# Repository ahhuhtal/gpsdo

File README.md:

# GPS discliplined oscillator

Contained in this repository are the source code and PCB design files for my GPS disciplined oscillator project.

The GPSDO uses the one pulse per second (PPS) output of a GPS receiver to continuously adjust an OSC5A2B02 oven-controller crystal oscillator to keep it phase-locked with GPS time.

This gives a stable (both short term and long) 10 MHz time base for measurement instruments.

An important design goal has been to keep the cost very low.

Some more information is available at https://kiedontaa.blogspot.com/2025/02/gps-disciplined-oscillator-part-2.html

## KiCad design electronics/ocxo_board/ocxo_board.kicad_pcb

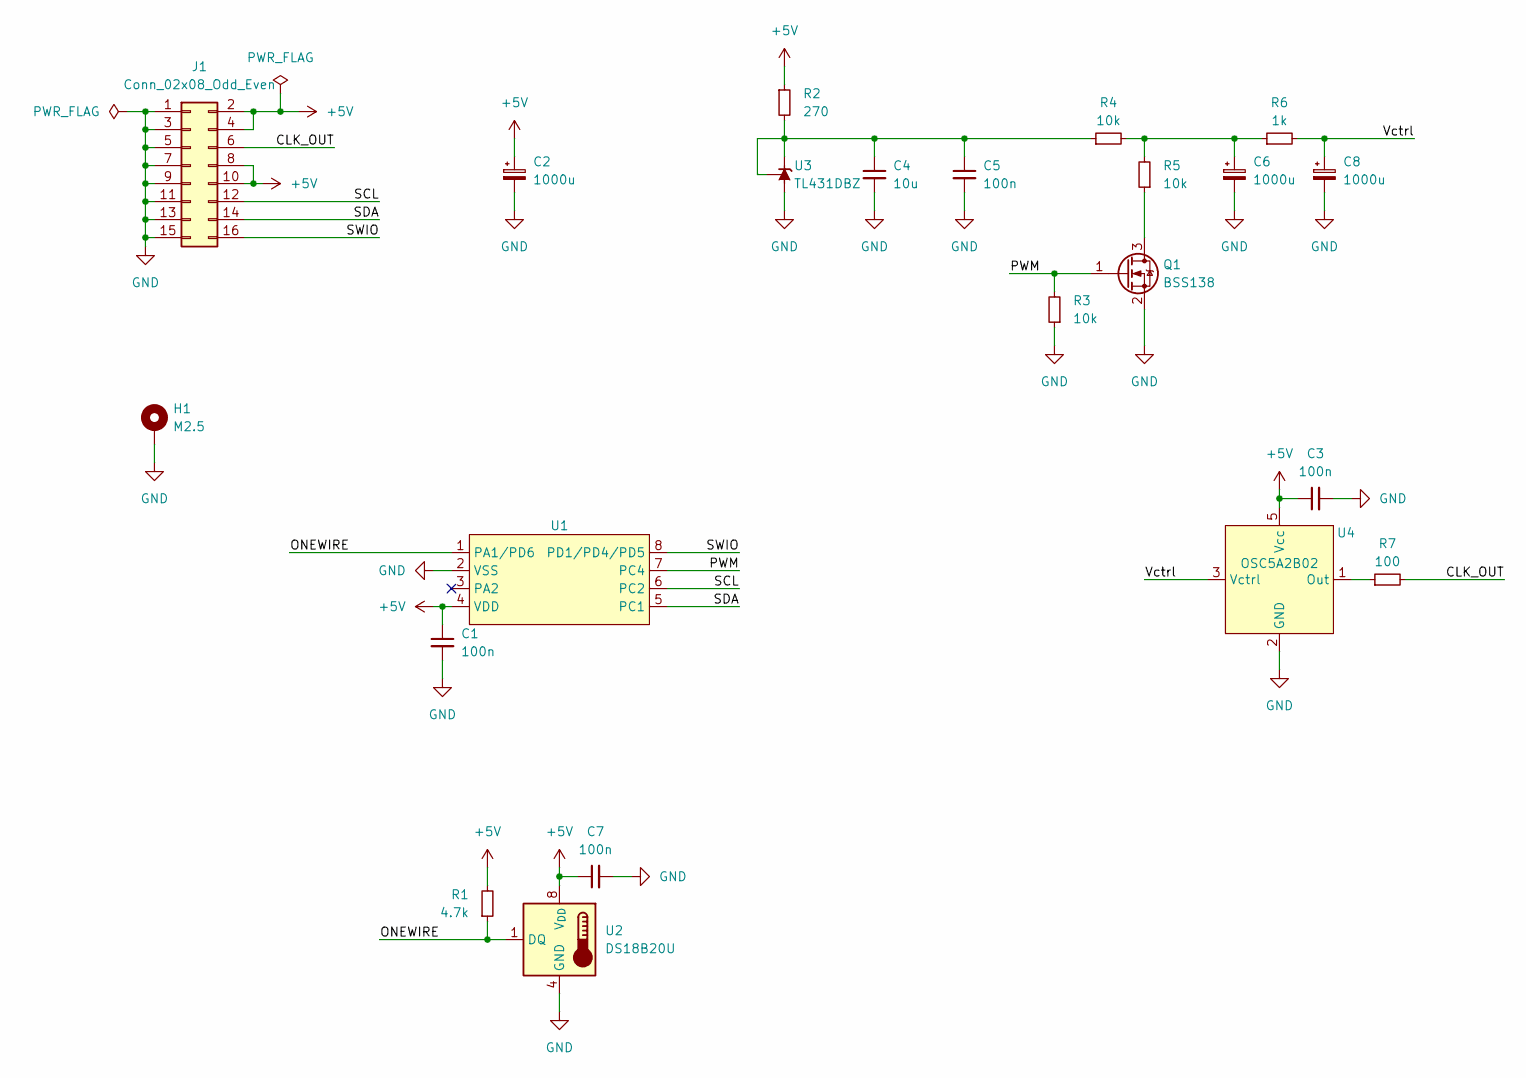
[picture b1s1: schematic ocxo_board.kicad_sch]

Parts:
C1, C3, C5, C7: 100n; C_0805_2012Metric_Pad1.18x1.45mm_HandSolder
C2, C6, C8: 1000u; CP_Radial_D8.0mm_P3.50mm
C4: 10u; C_0805_2012Metric_Pad1.18x1.45mm_HandSolder
H1: M2.5; MountingHole_2.7mm_M2.5_DIN965_Pad
J1: Conn_02x08_Odd_Even; IDC-Header_2x08_P2.54mm_Vertical
Q1: BSS138; SOT-23
R1: 4.7k; R_0805_2012Metric_Pad1.20x1.40mm_HandSolder
R2: 270; R_0805_2012Metric_Pad1.20x1.40mm_HandSolder
R3, R4, R5: 10k; R_0805_2012Metric_Pad1.20x1.40mm_HandSolder
R6: 1k; R_0805_2012Metric_Pad1.20x1.40mm_HandSolder
R7: 100; R_0805_2012Metric_Pad1.20x1.40mm_HandSolder
U1: SOP-8_3.9x4.9mm_P1.27mm
U2: DS18B20U; MSOP-8_3x3mm_P0.65mm
U3: TL431DBZ; SOT-23
U4: OSC5A2B02

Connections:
+5V: C1.1, C2.1, C3.1, C7.1, J1.2, J1.4, J1.8, J1.10, R1.2, R2.1, U1.4 (VDD), U2.8 (V_{DD}), U4.5 (Vcc)
/CLK_OUT: J1.6, R7.2
/ONEWIRE: R1.1, U1.1 (PA1/PD6), U2.1 (DQ)
/PWM: Q1.1 (G), R3.2, U1.7 (PC4)
/SCL: J1.12, U1.6 (PC2)
/SDA: J1.14, U1.5 (PC1)
/SWIO: J1.16, U1.8 (PD1/PD4/PD5)
/Vctrl: C8.1, R6.2, U4.3 (Vctrl)
GND: C1.2, C2.2, C3.2, C4.2, C5.2, C6.2, C7.2, C8.2, H1.1, J1.1, J1.3, J1.5, J1.7, J1.9, J1.11, J1.13, J1.15, Q1.2 (S), R3.1, U1.2 (VSS), U2.4 (GND), U3.3 (A), U4.2 (GND)
unnamed: C6.1, R4.2, R5.2, R6.1
unnamed: Q1.3 (D), R5.1
unnamed: C4.1, C5.1, R2.2, R4.1, U3.1 (K), U3.2 (REF)
unnamed: R7.1, U4.1 (Out)

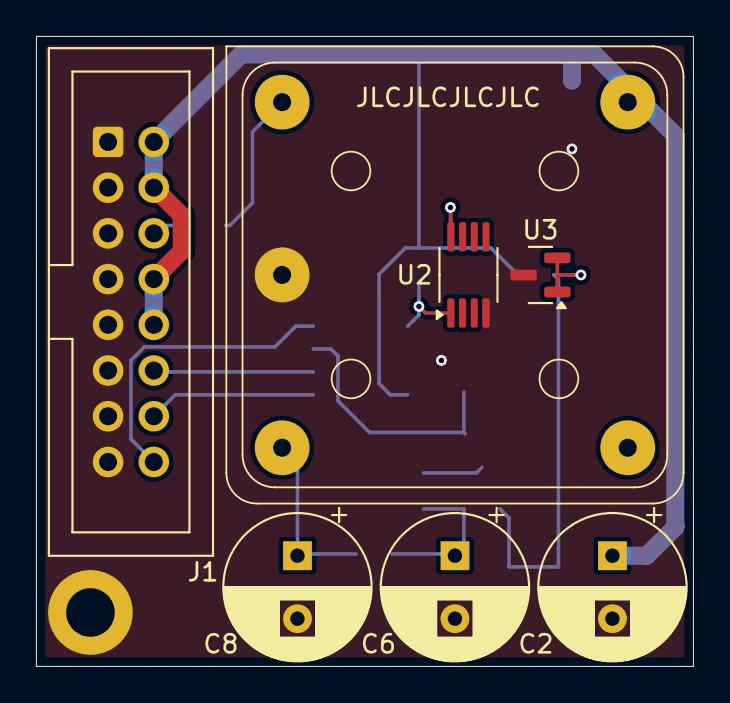
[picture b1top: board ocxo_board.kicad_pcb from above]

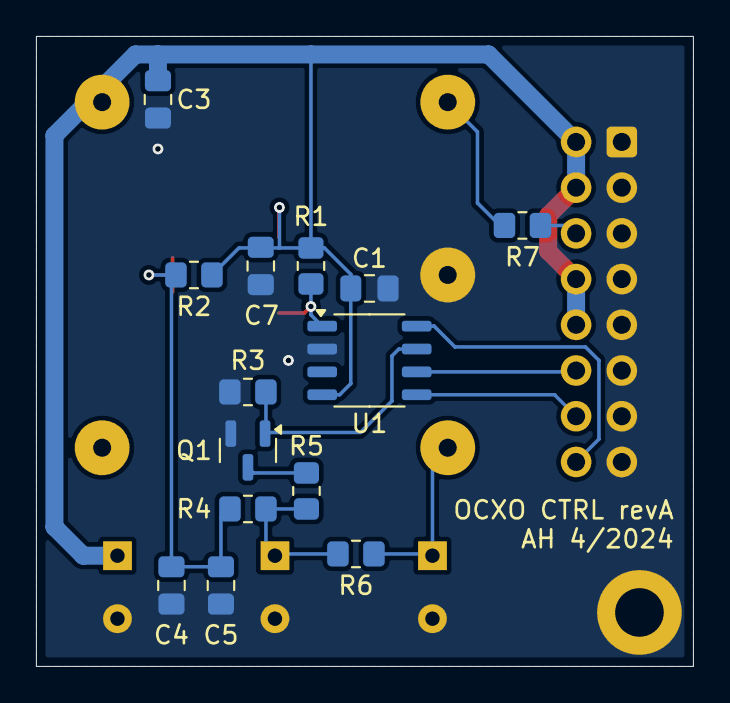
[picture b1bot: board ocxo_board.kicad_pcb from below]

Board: 2 copper layers, 36.5 x 35.0 mm, 22 parts (14 on the bottom side), 13 nets.

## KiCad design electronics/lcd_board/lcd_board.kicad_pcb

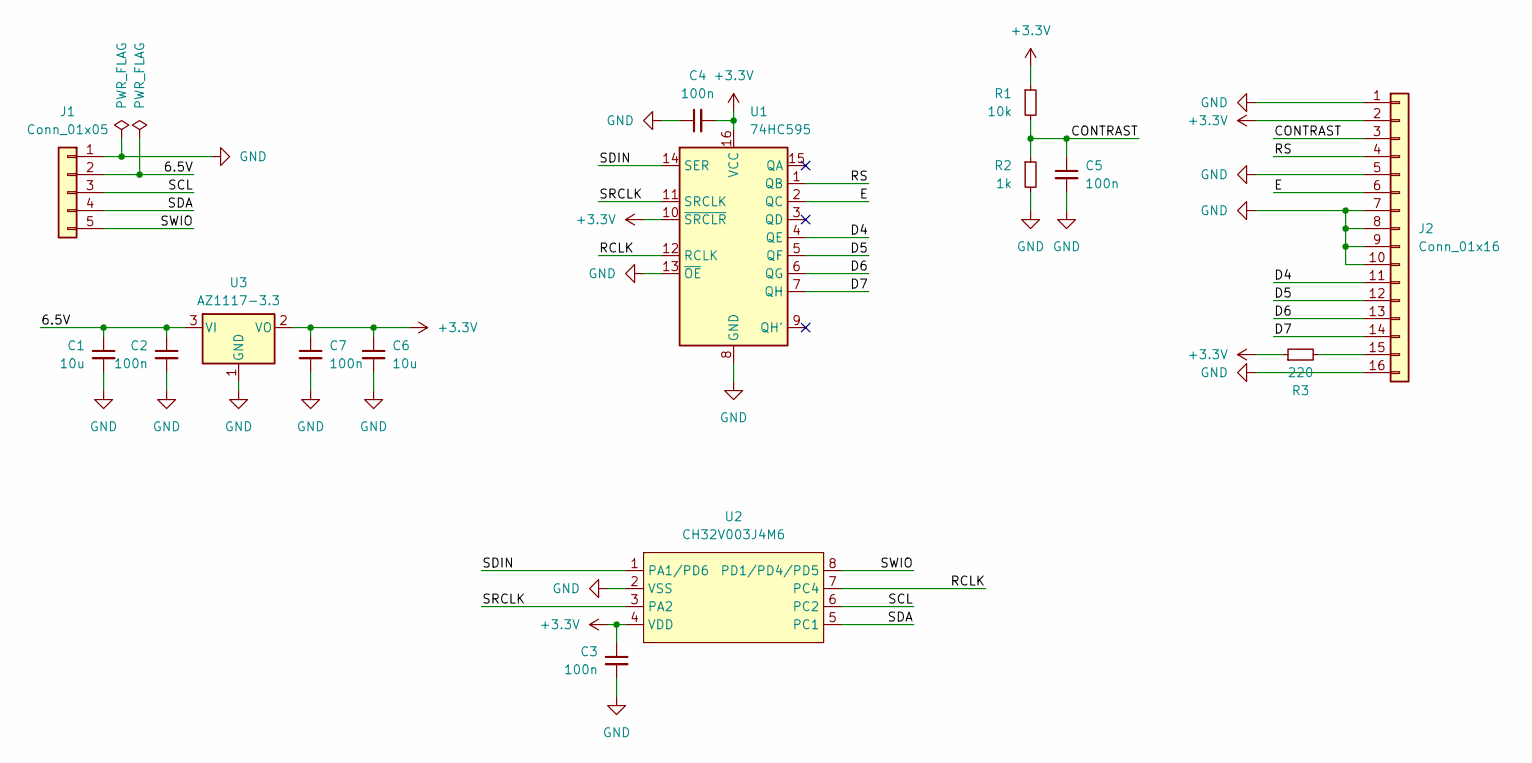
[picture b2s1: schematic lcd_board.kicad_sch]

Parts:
C1, C6: 10u; C_0805_2012Metric_Pad1.18x1.45mm_HandSolder
C2, C3, C4, C5, C7: 100n; C_0805_2012Metric_Pad1.18x1.45mm_HandSolder
J1: Conn_01x05; JST_PH_B5B-PH-K_1x05_P2.00mm_Vertical
J2: Conn_01x16; PinHeader_1x16_P2.54mm_Vertical
R1: 10k; R_0805_2012Metric_Pad1.20x1.40mm_HandSolder
R2: 1k; R_0805_2012Metric_Pad1.20x1.40mm_HandSolder
R3: 220; R_0805_2012Metric_Pad1.20x1.40mm_HandSolder
U1: 74HC595; SOIC-16_3.9x9.9mm_P1.27mm
U2: CH32V003J4M6; SOP-8_3.9x4.9mm_P1.27mm
U3: AZ1117-3.3; SOT-223-3_TabPin2

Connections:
+3.3V: C3.1, C4.2, C6.1, C7.1, J2.2, R1.1, R3.1, U1.10 (~SRCLR), U1.16 (VCC), U2.4 (VDD), U3.2 (VO)
/6.5V: C1.1, C2.1, J1.2, U3.3 (VI)
/CONTRAST: C5.1, J2.3, R1.2, R2.1
/D4: J2.11, U1.4 (QE)
/D5: J2.12, U1.5 (QF)
/D6: J2.13, U1.6 (QG)
/D7: J2.14, U1.7 (QH)
/E: J2.6, U1.2 (QC)
/RCLK: U1.12 (RCLK), U2.7 (PC4)
/RS: J2.4, U1.1 (QB)
/SCL: J1.3, U2.6 (PC2)
/SDA: J1.4, U2.5 (PC1)
/SDIN: U1.14 (SER), U2.1 (PA1/PD6)
/SRCLK: U1.11 (SRCLK), U2.3 (PA2)
/SWIO: J1.5, U2.8 (PD1/PD4/PD5)
GND: C1.2, C2.2, C3.2, C4.1, C5.2, C6.2, C7.2, J1.1, J2.1, J2.5, J2.7, J2.8, J2.9, J2.10, J2.16, R2.2, U1.8 (GND), U1.13 (~OE), U2.2 (VSS), U3.1 (GND)
unnamed: J2.15, R3.2

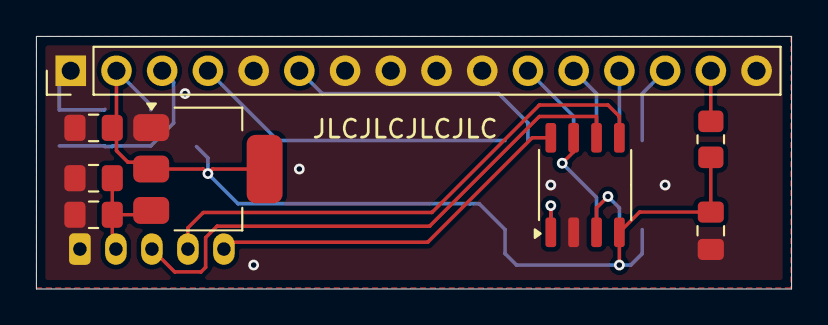
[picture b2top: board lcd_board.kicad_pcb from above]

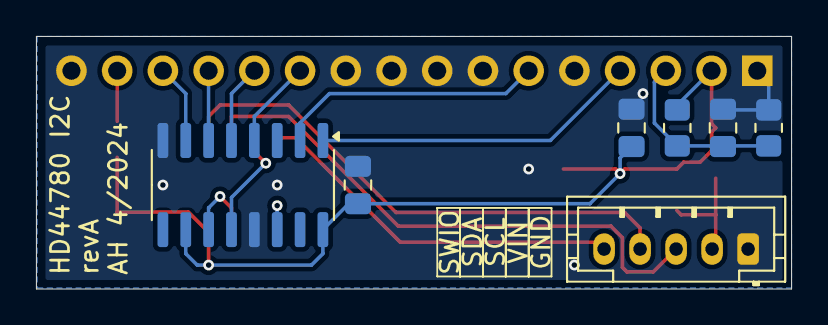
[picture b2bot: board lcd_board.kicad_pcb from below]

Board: 2 copper layers, 41.9 x 14.0 mm, 15 parts (7 on the bottom side), 17 nets.

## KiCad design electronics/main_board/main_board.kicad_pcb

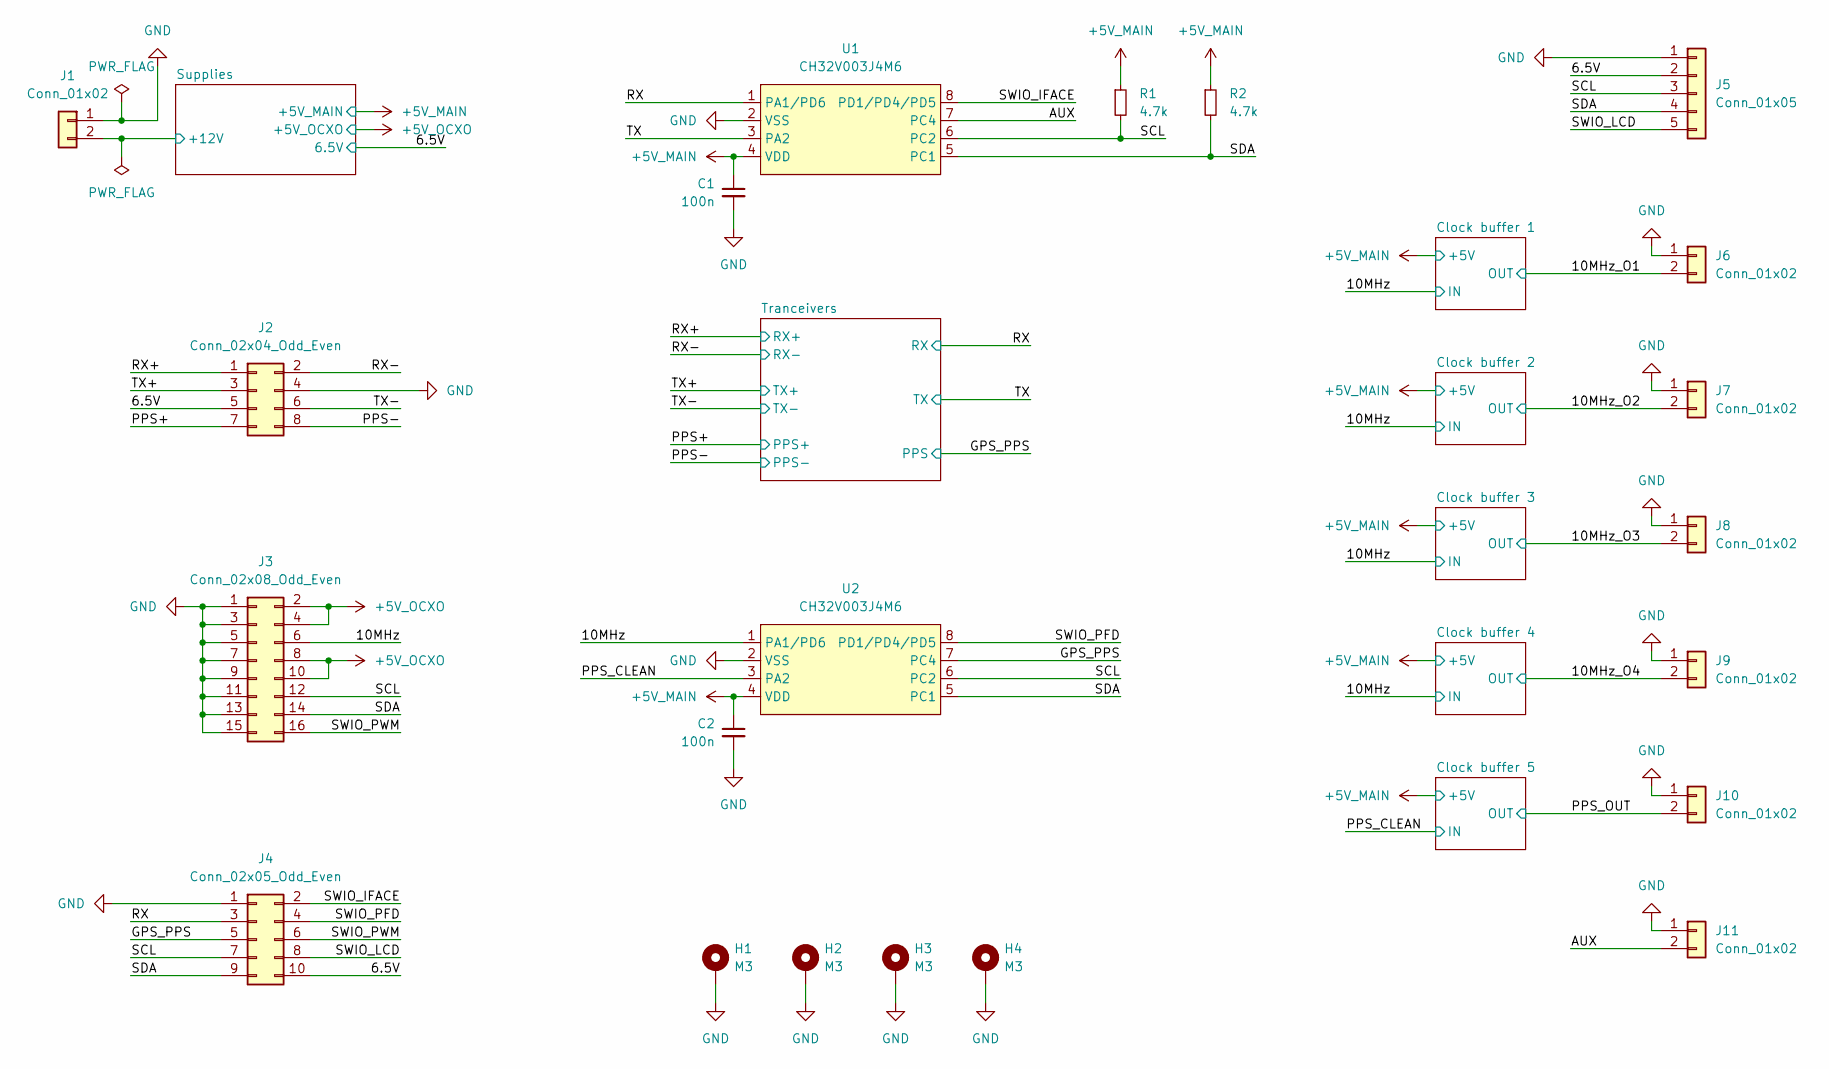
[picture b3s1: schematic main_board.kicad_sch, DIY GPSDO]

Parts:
C1, C2: 100n; C_0805_2012Metric_Pad1.18x1.45mm_HandSolder
H1, H2, H3, H4: M3; MountingHole_3.2mm_M3_DIN965_Pad
J1, J6, J7, J8, J9, J10, J11: Conn_01x02; JST_PH_B2B-PH-K_1x02_P2.00mm_Vertical
J2: Conn_02x04_Odd_Even; IDC-Header_2x04_P2.54mm_Vertical
J3: Conn_02x08_Odd_Even; IDC-Header_2x08_P2.54mm_Vertical
J4: Conn_02x05_Odd_Even; IDC-Header_2x05_P2.54mm_Vertical
J5: Conn_01x05; JST_PH_B5B-PH-K_1x05_P2.00mm_Vertical
R1, R2: 4.7k; R_0805_2012Metric_Pad1.20x1.40mm_HandSolder
U1, U2: CH32V003J4M6; SOP-8_3.9x4.9mm_P1.27mm

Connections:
+5V_MAIN: C1.1, C2.1, R1.1, R2.1, U1.4 (VDD), U2.4 (VDD); also elsewhere on the board
+5V_OCXO: J3.2, J3.4, J3.8, J3.10; also elsewhere on the board
/6.5V: J2.5, J4.10, J5.2; also elsewhere on the board
/10MHz: J3.6, U2.1 (PA1/PD6); also elsewhere on the board
/10MHz_O1: J6.2; also elsewhere on the board
/10MHz_O2: J7.2; also elsewhere on the board
/10MHz_O3: J8.2; also elsewhere on the board
/10MHz_O4: J9.2; also elsewhere on the board
/AUX: J11.2, U1.7 (PC4)
/GPS_PPS: J4.5, U2.7 (PC4); also elsewhere on the board
/PPS+: J2.7; also elsewhere on the board
/PPS-: J2.8; also elsewhere on the board
/PPS_CLEAN: U2.3 (PA2); also elsewhere on the board
/PPS_OUT: J10.2; also elsewhere on the board
/RX: J4.3, U1.1 (PA1/PD6); also elsewhere on the board
/RX+: J2.1; also elsewhere on the board
/RX-: J2.2; also elsewhere on the board
/SCL: J3.12, J4.7, J5.3, R1.2, U1.6 (PC2), U2.6 (PC2)
/SDA: J3.14, J4.9, J5.4, R2.2, U1.5 (PC1), U2.5 (PC1)
/SWIO_IFACE: J4.2, U1.8 (PD1/PD4/PD5)
/SWIO_LCD: J4.8, J5.5
/SWIO_PFD: J4.4, U2.8 (PD1/PD4/PD5)
/SWIO_PWM: J3.16, J4.6
/Supplies/+12V: J1.2; also elsewhere on the board
/TX: U1.3 (PA2); also elsewhere on the board
/TX+: J2.3; also elsewhere on the board
/TX-: J2.6; also elsewhere on the board
GND: C1.2, C2.2, H1.1, H2.1, H3.1, H4.1, J1.1, J2.4, J3.1, J3.3, J3.5, J3.7, J3.9, J3.11, J3.13, J3.15, J4.1, J5.1, J6.1, J7.1, J8.1, J9.1, J10.1, J11.1, U1.2 (VSS), U2.2 (VSS); also elsewhere on the board

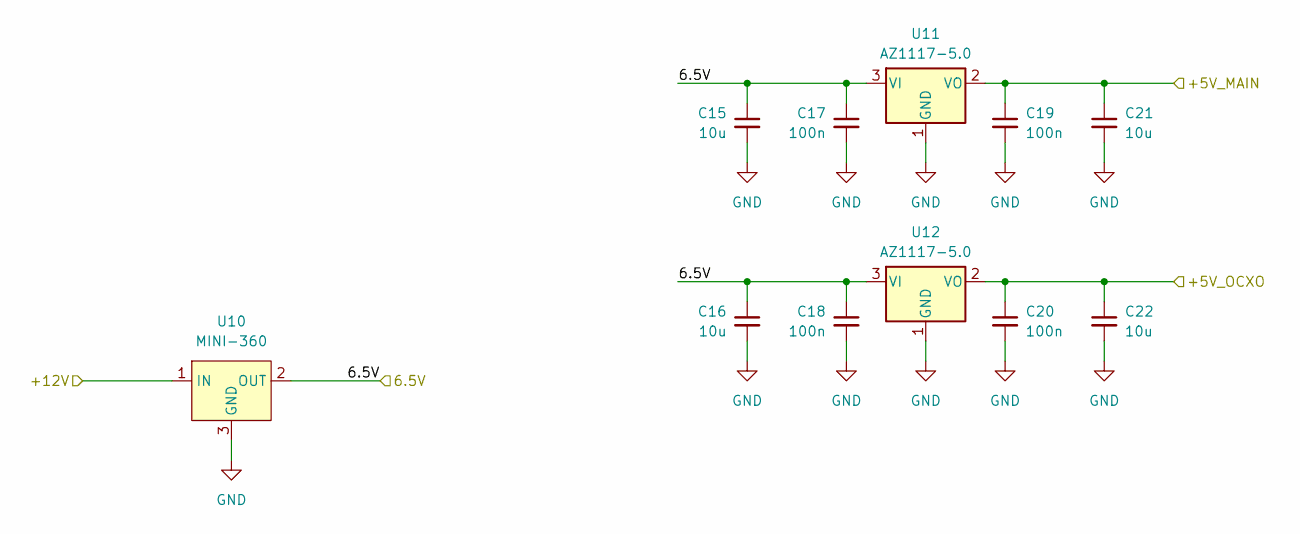
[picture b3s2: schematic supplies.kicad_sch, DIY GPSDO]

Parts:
C15, C16, C21, C22: 10u; C_0805_2012Metric_Pad1.18x1.45mm_HandSolder
C17, C18, C19, C20: 100n; C_0805_2012Metric_Pad1.18x1.45mm_HandSolder
U10: MINI-360
U11, U12: AZ1117-5.0; TO-252-2

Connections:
+5V_MAIN: C19.1, C21.1, U11.2 (VO); also elsewhere on the board
+5V_OCXO: C20.1, C22.1, U12.2 (VO); also elsewhere on the board
/6.5V: C15.1, C16.1, C17.1, C18.1, U10.2 (OUT), U11.3 (VI), U12.3 (VI); also elsewhere on the board
/Supplies/+12V: U10.1 (IN); also elsewhere on the board
GND: C15.2, C16.2, C17.2, C18.2, C19.2, C20.2, C21.2, C22.2, U10.3 (GND), U11.1 (GND), U12.1 (GND); also elsewhere on the board

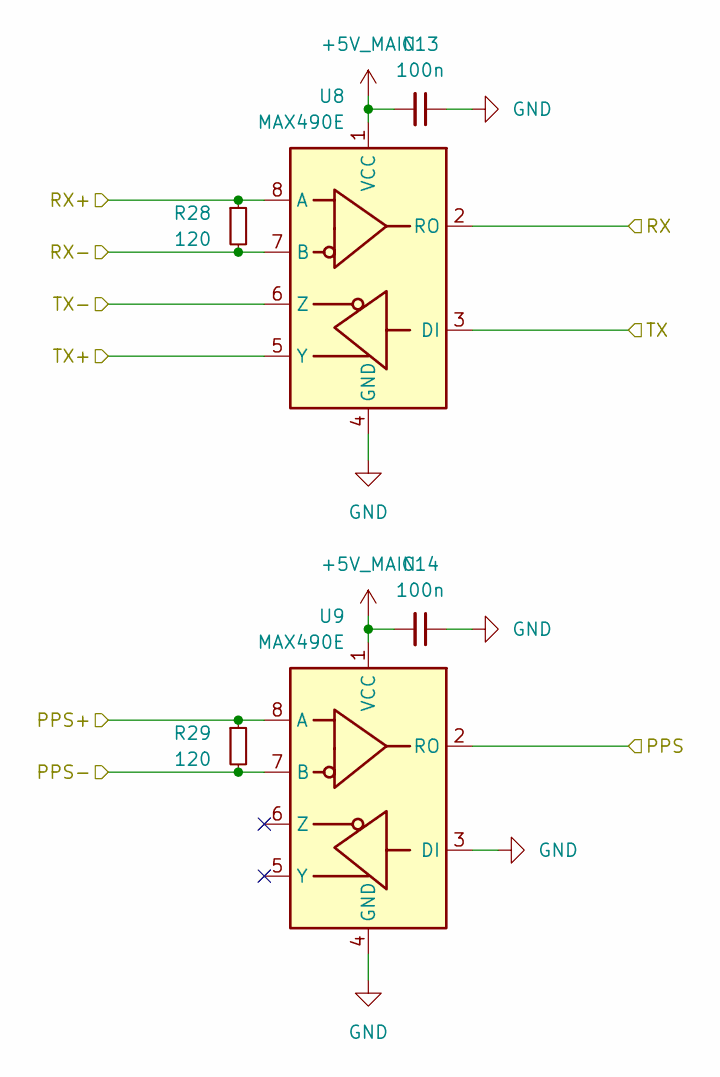
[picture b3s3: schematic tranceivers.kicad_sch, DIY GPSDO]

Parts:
C13, C14: 100n; C_0805_2012Metric_Pad1.18x1.45mm_HandSolder
R28, R29: 120; R_0805_2012Metric_Pad1.20x1.40mm_HandSolder
U8, U9: MAX490E; SOIC-8_3.9x4.9mm_P1.27mm

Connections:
+5V_MAIN: C13.2, C14.2, U8.1 (VCC), U9.1 (VCC); also elsewhere on the board
/GPS_PPS: U9.2 (RO); also elsewhere on the board
/PPS+: R29.1, U9.8 (A); also elsewhere on the board
/PPS-: R29.2, U9.7 (B); also elsewhere on the board
/RX: U8.2 (RO); also elsewhere on the board
/RX+: R28.1, U8.8 (A); also elsewhere on the board
/RX-: R28.2, U8.7 (B); also elsewhere on the board
/TX: U8.3 (DI); also elsewhere on the board
/TX+: U8.5 (Y); also elsewhere on the board
/TX-: U8.6 (Z); also elsewhere on the board
GND: C13.1, C14.1, U8.4 (GND), U9.3 (DI), U9.4 (GND); also elsewhere on the board

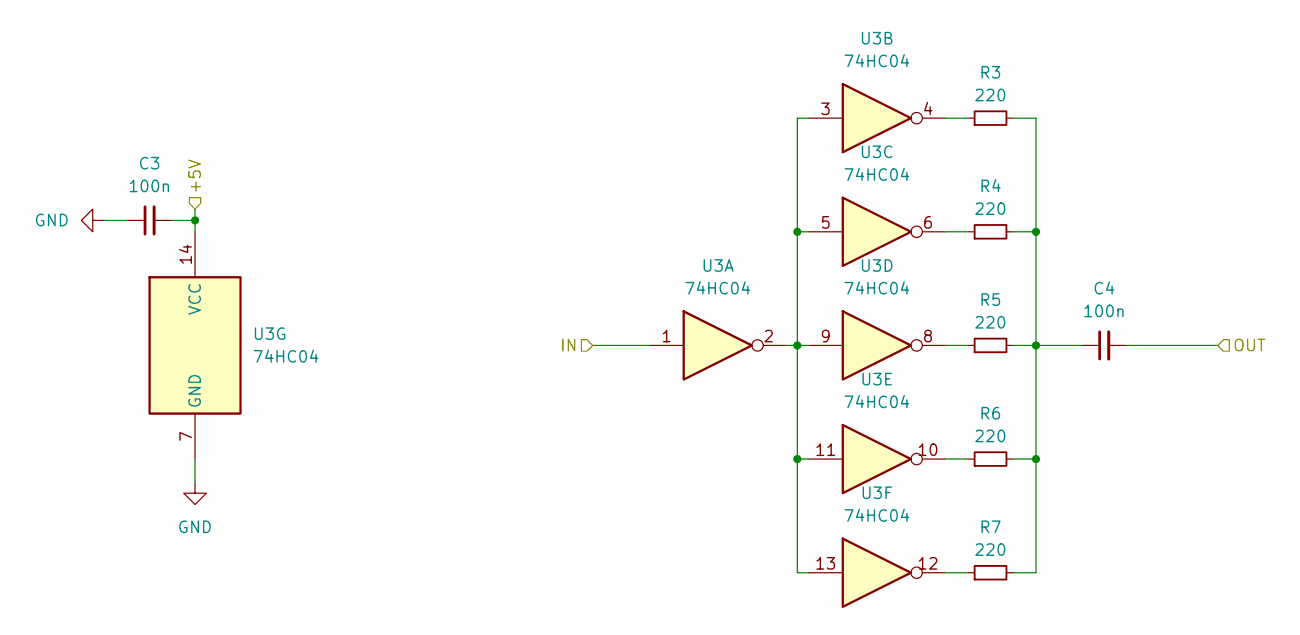
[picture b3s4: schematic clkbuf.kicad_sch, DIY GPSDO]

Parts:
C3, C4: 100n; C_0805_2012Metric_Pad1.18x1.45mm_HandSolder
R3, R4, R5, R6, R7: 220; R_0805_2012Metric_Pad1.20x1.40mm_HandSolder
U3: 74HC04; SOIC-14_3.9x8.7mm_P1.27mm

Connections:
+5V_MAIN: C3.2, U3.14 (VCC); also elsewhere on the board
/10MHz: U3.1; also elsewhere on the board
/10MHz_O1: C4.2; also elsewhere on the board
GND: C3.1, U3.7 (GND); also elsewhere on the board
unnamed: C4.1, R3.2, R4.2, R5.2, R6.2, R7.2
unnamed: R3.1, U3.4
unnamed: R4.1, U3.6
unnamed: R5.1, U3.8
unnamed: R6.1, U3.10
unnamed: R7.1, U3.12
unnamed: U3.2, U3.3, U3.5, U3.9, U3.11, U3.13

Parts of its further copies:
C5, C6, C7, C8, C9, C10, C11, C12: 100n; C_0805_2012Metric_Pad1.18x1.45mm_HandSolder
R8, R9, R10, R11, R12, R13, R14, R15, R16, R17, R18, R19, R20, R21, R22, R23, R24, R25, R26, R27: 220; R_0805_2012Metric_Pad1.20x1.40mm_HandSolder
U4, U5, U6, U7: 74HC04; SOIC-14_3.9x8.7mm_P1.27mm

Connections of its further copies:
+5V_MAIN: C5.2, C7.2, C9.2, C11.2, U4.14 (VCC), U5.14 (VCC), U6.14 (VCC), U7.14 (VCC); also elsewhere on the board
/10MHz: U4.1, U5.1, U6.1; also elsewhere on the board
/10MHz_O2: C6.2; also elsewhere on the board
/10MHz_O3: C8.2; also elsewhere on the board
/10MHz_O4: C10.2; also elsewhere on the board
/PPS_CLEAN: U7.1; also elsewhere on the board
/PPS_OUT: C12.2; also elsewhere on the board
GND: C5.1, C7.1, C9.1, C11.1, U4.7 (GND), U5.7 (GND), U6.7 (GND), U7.7 (GND); also elsewhere on the board
unnamed: C6.1, R8.2, R9.2, R10.2, R11.2, R12.2
unnamed: C8.1, R13.2, R14.2, R15.2, R16.2, R17.2
unnamed: C10.1, R18.2, R19.2, R20.2, R21.2, R22.2
unnamed: C12.1, R23.2, R24.2, R25.2, R26.2, R27.2
unnamed: R8.1, U4.4
unnamed: R9.1, U4.6
unnamed: R10.1, U4.8
unnamed: R11.1, U4.10
unnamed: R12.1, U4.12
unnamed: R13.1, U5.4
unnamed: R14.1, U5.6
unnamed: R15.1, U5.8
unnamed: R16.1, U5.10
unnamed: R17.1, U5.12
unnamed: R18.1, U6.4
unnamed: R19.1, U6.6
unnamed: R20.1, U6.8
unnamed: R21.1, U6.10
unnamed: R22.1, U6.12
unnamed: R23.1, U7.4
unnamed: R24.1, U7.6
unnamed: R25.1, U7.8
unnamed: R26.1, U7.10
unnamed: R27.1, U7.12
unnamed: U4.2, U4.3, U4.5, U4.9, U4.11, U4.13
unnamed: U5.2, U5.3, U5.5, U5.9, U5.11, U5.13
unnamed: U6.2, U6.3, U6.5, U6.9, U6.11, U6.13
unnamed: U7.2, U7.3, U7.5, U7.9, U7.11, U7.13

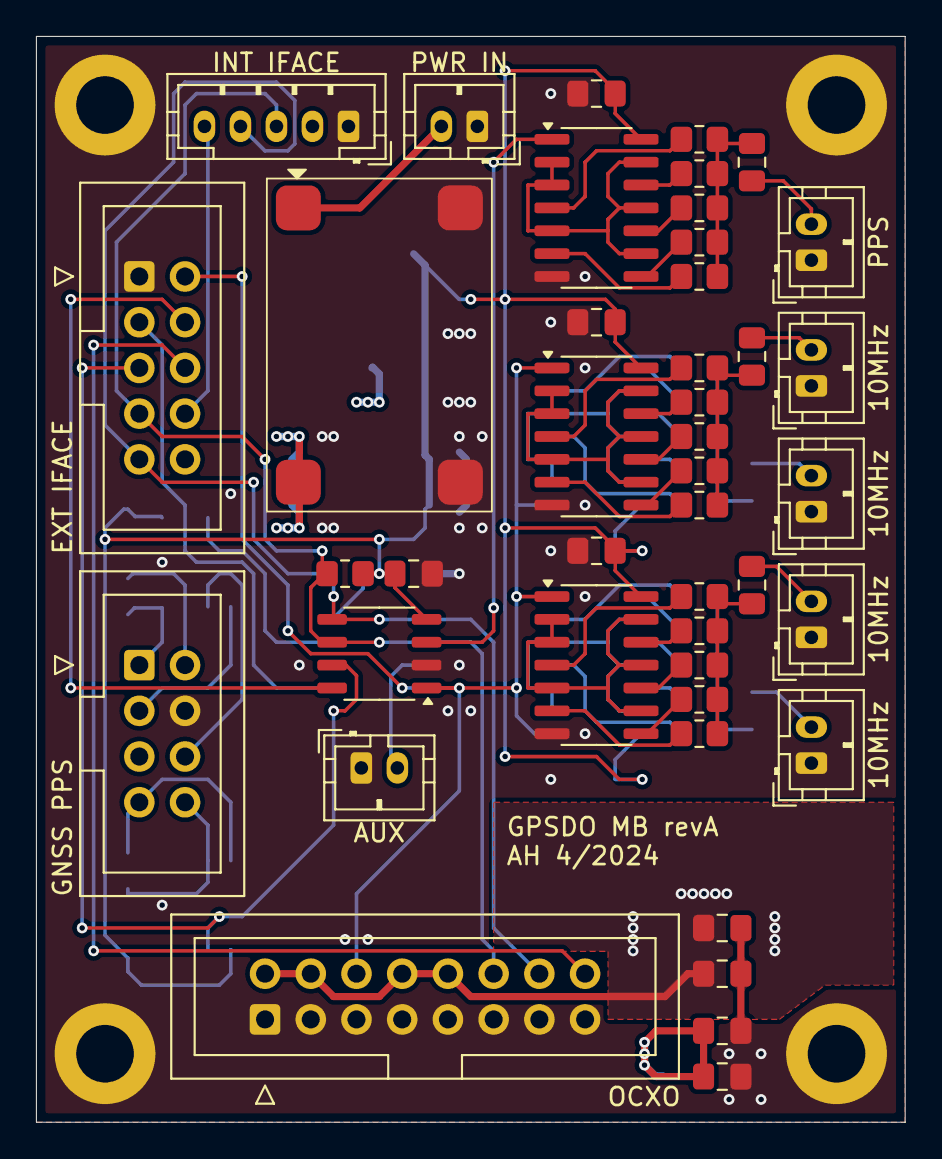
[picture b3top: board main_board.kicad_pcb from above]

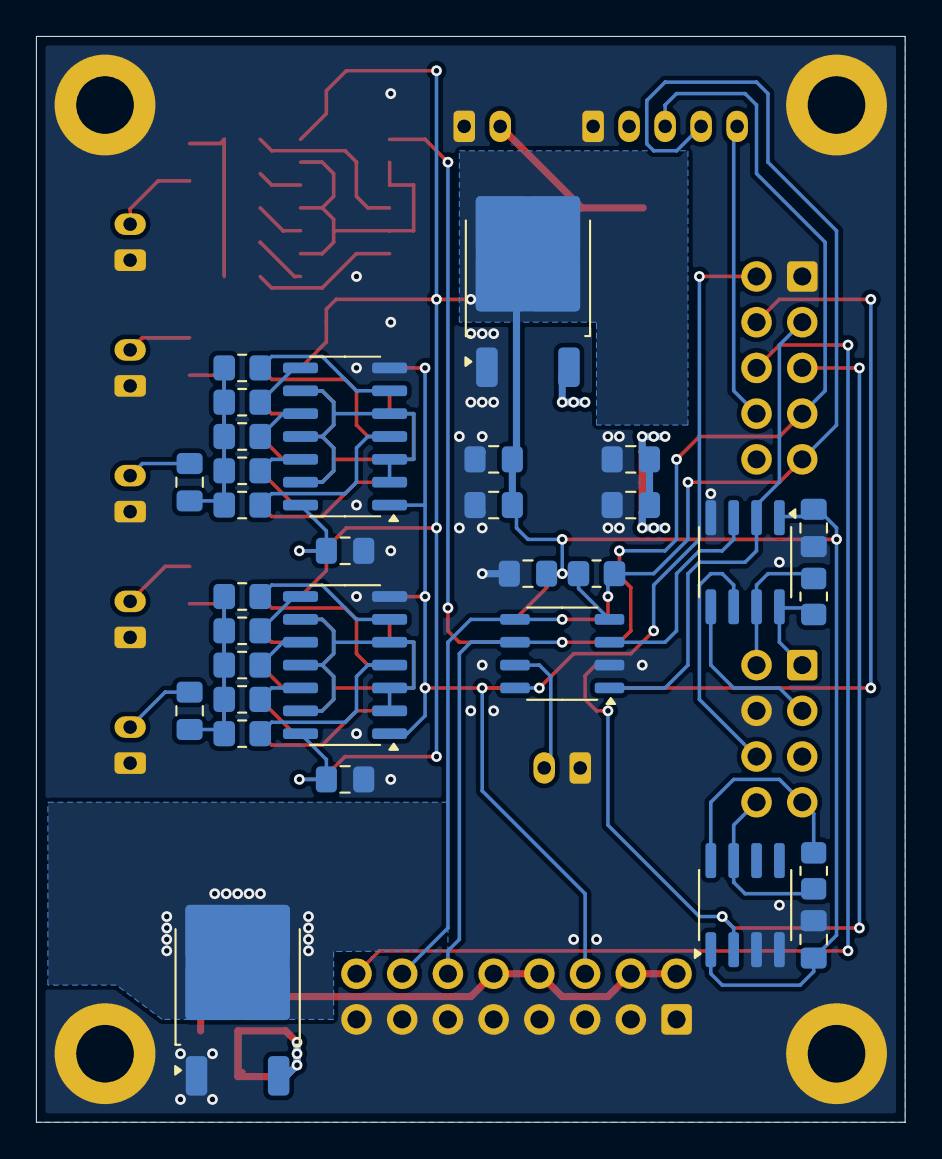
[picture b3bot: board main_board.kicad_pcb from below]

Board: 4 copper layers, 48.3 x 60.3 mm, 78 parts (31 on the bottom side), 63 nets.

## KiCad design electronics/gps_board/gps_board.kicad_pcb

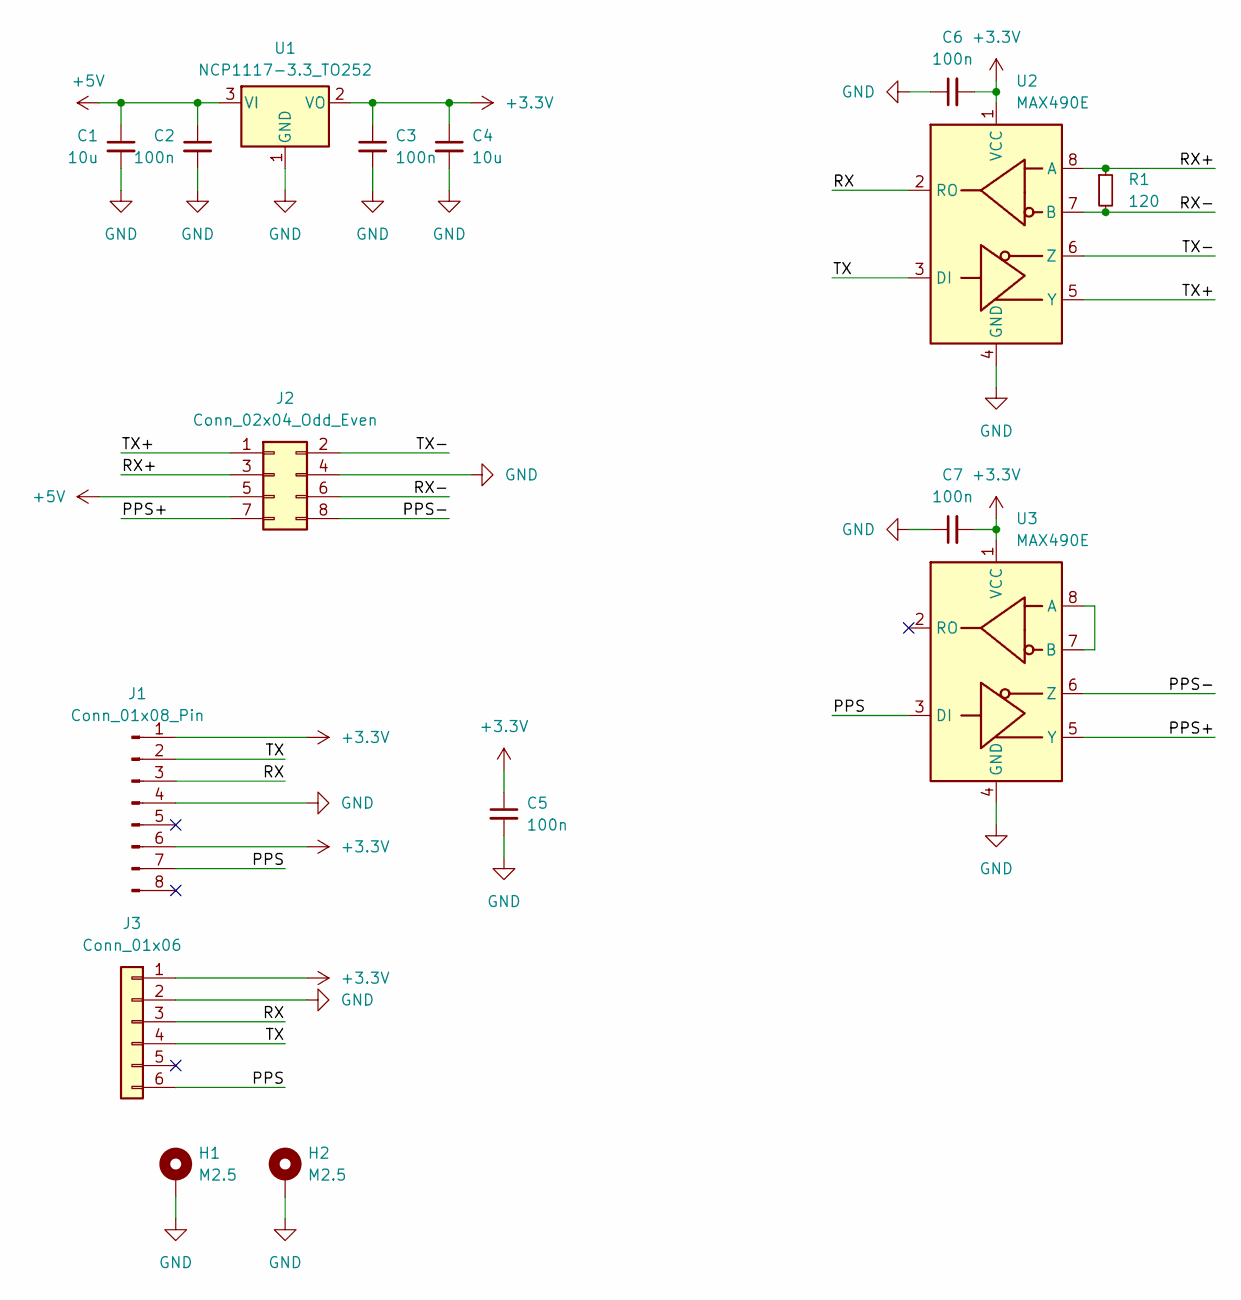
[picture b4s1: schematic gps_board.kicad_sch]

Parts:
C1, C4: 10u; C_0805_2012Metric_Pad1.18x1.45mm_HandSolder
C2, C3, C5, C6, C7: 100n; C_0805_2012Metric_Pad1.18x1.45mm_HandSolder
H1, H2: M2.5; MountingHole_2.7mm_M2.5_DIN965_Pad
J1: Conn_01x08_Pin; PinHeader_1x08_P1.27mm_Vertical
J2: Conn_02x04_Odd_Even; IDC-Header_2x04_P2.54mm_Vertical
J3: Conn_01x06; JST_PH_B6B-PH-K_1x06_P2.00mm_Vertical
R1: 120; R_0805_2012Metric_Pad1.20x1.40mm_HandSolder
U1: NCP1117-3.3_TO252; TO-252-2
U2, U3: MAX490E; SOIC-8_3.9x4.9mm_P1.27mm

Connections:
+3.3V: C3.1, C4.1, C5.1, C6.2, C7.2, J1.1, J1.6, J3.1, U1.2 (VO), U2.1 (VCC), U3.1 (VCC)
+5V: C1.1, C2.1, J2.5, U1.3 (VI)
/PPS: J1.7, J3.6, U3.3 (DI)
/PPS+: J2.7, U3.5 (Y)
/PPS-: J2.8, U3.6 (Z)
/RX: J1.3, J3.3, U2.2 (RO)
/RX+: J2.3, R1.1, U2.8 (A)
/RX-: J2.6, R1.2, U2.7 (B)
/TX: J1.2, J3.4, U2.3 (DI)
/TX+: J2.1, U2.5 (Y)
/TX-: J2.2, U2.6 (Z)
GND: C1.2, C2.2, C3.2, C4.2, C5.2, C6.1, C7.1, H1.1, H2.1, J1.4, J2.4, J3.2, U1.1 (GND), U2.4 (GND), U3.4 (GND)
unnamed: U3.7 (B), U3.8 (A)

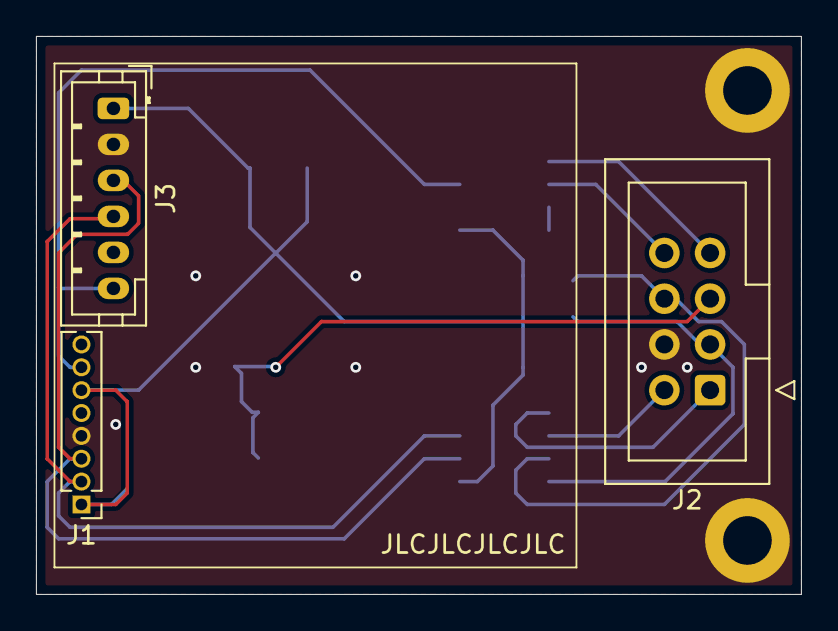
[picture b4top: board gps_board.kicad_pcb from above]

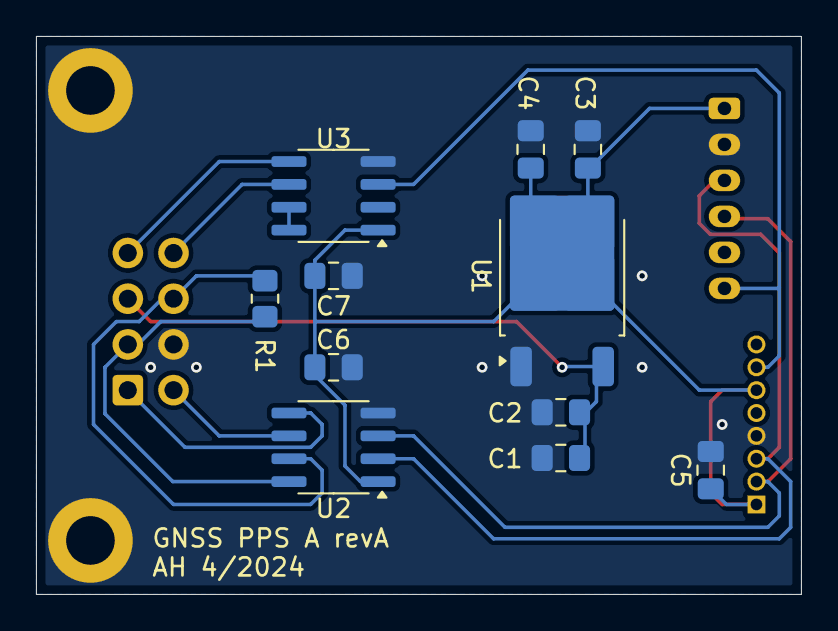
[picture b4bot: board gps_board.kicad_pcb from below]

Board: 2 copper layers, 42.5 x 31.0 mm, 16 parts (11 on the bottom side), 13 nets.

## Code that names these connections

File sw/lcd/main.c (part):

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 *    to display the data for the user.
 *
 * The HC595 is connected to the MCU as follows:
 *  PA2 --> SRCLK (shift clock)
 *  PA1 --> SDIN (shift data in)
 *  PC4 --> RCLK (latch clock)
 *
 * The HD44780 is connected to the HC595 as follows:
 *  QB (bit 1) --> RS
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 * @param val true for high, false for low
 */
static inline void set_595_clock(bool val) {
    // bit 18 is PA2 clear, bit 2 is PA2 set
    GPIOA->BSHR = (1 << 18) | (val ? (1 << 2) : 0);
}

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 * @param val true for high, false for low
 */
static inline void set_595_data(bool val) {
    // bit 17 is PA1 clear, bit 1 is PA1 set
    GPIOA->BSHR = (1 << 17) | (val ? (1 << 1) : 0);
}

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 * @param val true for high, false for low
 */
static inline void set_595_latch(bool val) {
    // bit 20 is PC4 clear, bit 4 is PC4 set
    GPIOC->BSHR = (1 << 20) | (val ? (1 << 4) : 0);
}

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
    RCC->APB2PCENR |= RCC_APB2Periph_GPIOA | RCC_APB2Periph_GPIOC;

    // PA1: 595 serial shift data
    GPIOA->CFGLR &= ~(0xf << (4*1));
    GPIOA->CFGLR |= (GPIO_Speed_10MHz | GPIO_CNF_OUT_PP) << (4*1);
    // PA2: 595 serial shift clock
    GPIOA->CFGLR &= ~(0xf << (4*2));
    GPIOA->CFGLR |= (GPIO_Speed_10MHz | GPIO_CNF_OUT_PP) << (4*2);
    // PC4: 595 latch clock
    GPIOC->CFGLR &= ~(0xf << (4*4));
    GPIOC->CFGLR |= (GPIO_Speed_10MHz | GPIO_CNF_OUT_PP) << (4*4);

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
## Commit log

2024-05-18 initial commit. not everything works.
2024-05-19 Initial working LCD support
2024-05-19 iface: use common I2C functions, separate data for push and pull push: timestamp value as soon as it arrives with validity pull: timestamp, latitude, longitude and number of satellites with validity
2024-05-25 Add utc_from_unix to time handling functions
2024-05-25 Add querying for master transfer errors
2024-05-25 iface: Make transfer buffers volatile
2024-05-25 iface: Explicitly choose GPS+BeiDou as constellation, but allow GPS only data too
2024-05-25 Switch to using common code base for I2C. Control update: Use first an FLL, then a fast PLL and finally a slow PLL. Provide status data via I2C when pulled.
2024-05-25 ocxo: Switch to using common code base for I2C
2025-02-22 Use ch32v003fun from submodule
2025-02-22 lcd, common: Add unixtime for UTC conversion. Implement UI display.
2025-02-22 ocxo_ctrl: Improve code quality and documentation
2025-02-22 pfd: Bias phase at transition point to achieve dithering
2025-02-22 pfd: Improve code quality and documentation
2025-02-22 common/i2c: Differentiate between errors, rename acquire and release calls
2025-02-22 common/i2c: Improve code quality and documentation
2025-02-22 iface: Improve code quality and documentation
2025-02-22 pfd: Add phase bias correction
2025-02-22 pfd: Attempt to solve the full tick counter race condition
2025-02-22 Add .gitignore
2025-02-22 Add ch32v003fun as submodule
2025-02-22 pfd: Move Kahan-Babushka sum to its own function
2025-02-22 pfd: Update OCXO gain value based on recent measurement result
2025-02-22 Update ch32v003fun
2025-02-22 Add global Makefile to build all components
2025-02-22 iface: Set data as invalid if data is not received for a while
2025-02-22 lcd: Improve code quality and documentation
2025-02-22 pfd: Revise multistep initial lock control, communication data format changes and PPS output
2025-03-15 pfd: Change control approach. Instead of fast control period with low-pass filtered inputs, use a slow control period with inputs averaged in between.
2025-03-15 lcd: Change documentation of data from PFD
2025-03-15 Move software under sw directory, to allow adding the HW files
2025-03-15 Add electronics design files
2025-03-15 Add mechanical files
2025-03-15 Add README.md
2025-06-30 Add sw/support for supporting Pythons scripts
2025-07-01 pfd: Revise control, revise phase estimation, improve documentation Control, FLL: Use estimated phase, instead of ticks, to compute frequency. Revise logic for switching averaging period. Control, PL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
2025-07-01 Add sw/doc for documentation. Add first version of ICD to doc.
2025-07-01 Update ch32v003fun to latest
2025-07-03 lcd: Show graphical history of OCXO control word
2026-06-23 Add license notice
2026-06-23 lcd: Add long and short history graphs of multiple parameters
